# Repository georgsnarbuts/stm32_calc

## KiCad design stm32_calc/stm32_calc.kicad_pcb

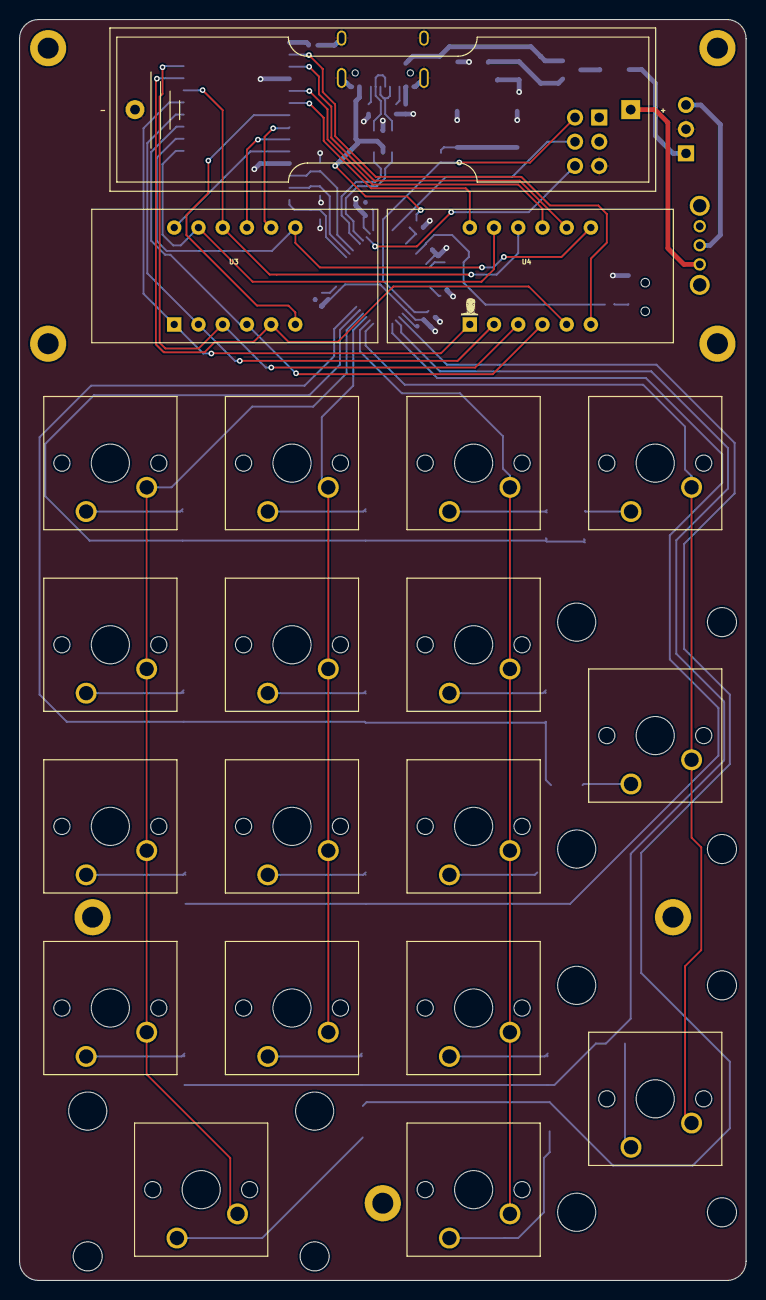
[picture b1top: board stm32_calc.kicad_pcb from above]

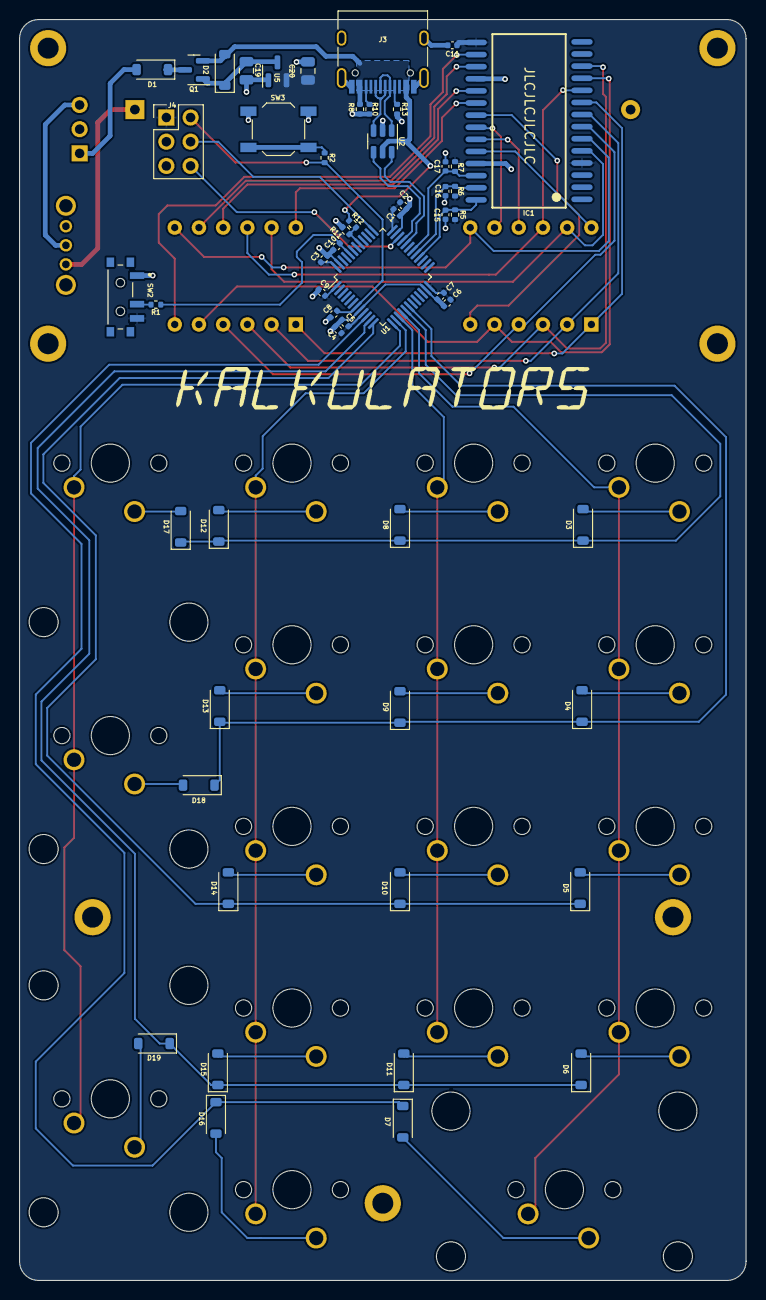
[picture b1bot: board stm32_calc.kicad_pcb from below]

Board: 2 copper layers, 76.2 x 132.2 mm, 83 parts (54 on the bottom side), 66 nets.

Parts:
BT1: Battery_Cell; BatteryHolder_Keystone_2460_1xAA
C1, C3, C6, C9, C11: 100n; C_0402_1005Metric
C2, C7: 4.7u; C_0402_1005Metric
C4: 1u; C_0402_1005Metric
C5: 10n; C_0402_1005Metric
C8, C10: 0.1uF; C_0402_1005Metric
C15, C16, C17: 100pF; C_0402_1005Metric
C19, C20: 1u; C_0805_2012Metric
D1: schottky diode; D_SOD-123
D2: 1n4148; D_SOD-123
D3, D4, D5, D6, D7, D8, D9, D10, D11, D12, D13, D14, D15, D16, D17, D18, D19: 1N4148; D_SOD-123
H1, H2, H3, H4, H5, H6, H7: MountingHole_Pad; MountingHole_2.2mm_M2_DIN965_Pad
IC1: TM1638; SOP28 tm1638
J2: Conn_01x03; PinHeader_1x03_P2.54mm_Vertical
J3: C5307759; USB_C_Receptacle_HRO_TYPE-C-31-M-12
J4: Conn_02x03_Odd_Even; PinHeader_2x03_P2.54mm_Vertical
Q1: p channel mosfet sot 23; SOT-23
R1, R8: 10k; R_0402_1005Metric
R2: 100; R_0402_1005Metric
R5, R6, R7: 10K; R_0402_1005Metric
R10, R13: 5k1; R_0402_1005Metric
R11: 2k; R_0402_1005Metric
R12: 1k; R_0402_1005Metric
SW1: batter_switch; SK12D07VG4_slider
SW2: SS-1290; ss-1290
SW3: Reset; SW_SPST_TL3342
SW_clear1: SW_SPST; geo1.00u_PCB
SW_divide1: SW_SPST; geo1.00u_PCB
SW_eight1: SW_SPST; geo1.00u_PCB
SW_equals1: SW_SPST; geo2.00u_Vertical_PCB
SW_five1: SW_SPST; geo1.00u_PCB
SW_four1: SW_SPST; geo1.00u_PCB
SW_minus1: SW_SPST; geo1.00u_PCB
SW_mutiplicate1: SW_SPST; geo1.00u_PCB
SW_nine1: SW_SPST; geo1.00u_PCB
SW_one1: SW_SPST; geo1.00u_PCB
SW_plus1: SW_SPST; geo2.00u_Vertical_PCB
SW_point1: SW_SPST; geo1.00u_PCB
SW_seven1: SW_SPST; geo1.00u_PCB
SW_six1: SW_SPST; geo1.00u_PCB
SW_three1: SW_SPST; geo1.00u_PCB
SW_two1: SW_SPST; geo1.00u_PCB
SW_zero1: SW_SPST; geo2.00u_PCB
U1: STM32F072CBT6; LQFP-48_7x7mm_P0.5mm
U2: USBLC6-2SC6; SOT-23-6
U3, U4: CC56-12GWA; 7seg_sr410361n
U5: XC6206P332MR; SOT-23

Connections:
+3V3: C1.2, C2.2, C3.2, C4.2, C5.2, C6.2, C7.2, C9.2, C11.1, C20.1, IC1.4 (VCC), IC1.15 (VCC), J4.1, R5.2, R6.2, R7.2, SW2.3 (C), U1.1 (VBAT), U1.9 (VDDA), U1.24 (VDD), U1.36 (VDDIO2), U1.48 (VDD), U5.2 (VO)
+5V: C19.1, D2.1 (K), Q1.1 (D), U5.3 (VI)
BOOT0: C10.1, R1.2, U1.44 (BOOT0)
CLK: C16.2, IC1.27 (CLK), R6.1, U1.29 (TIM1_CH1/PA8)
D+: U1.33 (USB_DP/PA12), U2.4 (I/O2)
D-: U1.32 (USB_DM/TIM1_CH4/PA11), U2.6 (I/O1)
DIO: C17.2, IC1.26 (DIO), R7.1, U1.30 (TIM1_CH2/PA9)
GND: BT1.2 (-), C1.1, C2.1, C3.1, C4.1, C5.1, C6.1, C7.1, C8.2, C9.1, C10.2, C11.2, C15.1, C16.1, C17.1, C19.2, C20.2, IC1.18 (GND), IC1.25 (GND), J2.2, J3.A1 (GND), J3.A12 (GND), J3.B1 (GND), J3.B12 (GND), J3.S1 (SHIELD), J4.5, R8.2, R10.2, R11.1, R13.2, SW2.1 (A), SW3.1, U1.8 (VSSA), U1.23 (VSS), U1.35 (VSS), U1.47 (VSS), U2.2 (GND), U5.1 (GND)
GR1: IC1.5 (SEG1/KS1), U3.11 (a), U4.11 (a)
GR2: IC1.6 (SEG2/KS2), U3.7 (b), U4.7 (b)
GR3: IC1.7 (SEG3/KS3), U3.4 (c), U4.4 (c)
GR4: IC1.8 (SEG4/KS4), U3.2 (d), U4.2 (d)
GR5: IC1.9 (SEG5/KS5), U3.1 (e), U4.1 (e)
GR6: IC1.10 (SEG6/KS6), U3.10 (f), U4.10 (f)
GR7: IC1.11 (SEG7/KS7), U3.5 (g), U4.5 (g)
GR8: IC1.12 (SEG8/KS8), U3.3 (DPX), U4.3 (DPX)
NRST: C8.1, J4.2, R2.2, U1.7 (NRST)
unnamed: BT1.1 (+), SW1.1 (A)
unnamed: D1.2 (A), J2.1
unnamed: D1.1 (K), Q1.3 (S)
unnamed: D3.2 (A), SW_clear1.1 (A)
unnamed: D4.2 (A), SW_seven1.1 (A)
unnamed: D5.2 (A), SW_four1.1 (A)
unnamed: D6.2 (A), SW_one1.1 (A)
unnamed: D7.2 (A), SW_zero1.1 (A)
unnamed: D8.2 (A), SW_divide1.1 (A)
unnamed: D9.2 (A), SW_eight1.1 (A)
unnamed: D10.2 (A), SW_five1.1 (A)
unnamed: D11.2 (A), SW_two1.1 (A)
unnamed: D12.2 (A), SW_mutiplicate1.1 (A)
unnamed: D13.2 (A), SW_nine1.1 (A)
unnamed: D14.2 (A), SW_six1.1 (A)
unnamed: D15.2 (A), SW_three1.1 (A)
unnamed: D16.2 (A), SW_point1.1 (A)
unnamed: D17.2 (A), SW_minus1.1 (A)
unnamed: D18.2 (A), SW_plus1.1 (A)
unnamed: D19.2 (A), SW_equals1.1 (A)
unnamed: J2.3, SW1.2 (B)
unnamed: J3.A5 (CC1), R13.1
unnamed: J3.B5 (CC2), R10.1
unnamed: R2.1, SW3.2
unnamed: R1.1, SW2.2 (B)
SEG1: IC1.24 (GRID1), U3.12 (CC1)
SEG2: IC1.23 (GRID2), U3.9 (CC2)
SEG3: IC1.22 (GRID3), U3.8 (CC3)
SEG4: IC1.21 (GRID4), U3.6 (CC4)
SEG5: IC1.20 (GRID5), U4.12 (CC1)
SEG6: IC1.19 (GRID6), U4.9 (CC2)
SEG7: IC1.17 (GRID7), U4.8 (CC3)
SEG8: IC1.16 (GRID8), U4.6 (CC4)
STB: C15.2, IC1.28 (~STB), R5.1, U1.28 (SPI2_MOSI/I2S2_SD/PB15)
SWCLK: J4.4, U1.37 (SWCLK/PA14)
SWDIO: J4.6, U1.34 (SWDIO/PA13)
col0: SW_clear1.2 (B), SW_four1.2 (B), SW_one1.2 (B), SW_seven1.2 (B), SW_zero1.2 (B), U1.16 (PA6/ADC_IN6/TIM3_CH1/TIM16_CH1)
col1: SW_divide1.2 (B), SW_eight1.2 (B), SW_five1.2 (B), SW_two1.2 (B), U1.15 (PA5/ADC_IN5/DAC_OUT2)
col2: SW_mutiplicate1.2 (B), SW_nine1.2 (B), SW_point1.2 (B), SW_six1.2 (B), SW_three1.2 (B), U1.14 (PA4/TIM14_CH1/ADC_IN4)
col3: SW_equals1.2 (B), SW_minus1.2 (B), SW_plus1.2 (B), U1.13 (PA3/TIM15_CH2/ADC_IN3)
row0: D3.1 (K), D8.1 (K), D12.1 (K), D17.1 (K), U1.17 (PA7/TIM3_CH2/TIM14_CH1/ADC_IN7)
row1: D4.1 (K), D9.1 (K), D13.1 (K), D18.1 (K), U1.18 (PB0/TIM3_CH3/ADC_IN8)
row2: D5.1 (K), D10.1 (K), D14.1 (K), U1.12 (PA2/ADC_IN2)
row3: D6.1 (K), D11.1 (K), D15.1 (K), D19.1 (K), U1.11 (PA1/ADC_IN1)
row4: D7.1 (K), D16.1 (K), U1.10 (PA0/ADC_IN0)
usbD+: J3.A6 (D+), J3.B6 (D+), U2.3 (I/O2)
usbD-: J3.A7 (D-), J3.B7 (D-), U2.1 (I/O1)
usb_check_mcu: R11.2, R12.1, U1.41 (SPI1_MOSI/I2S1_SD/TIM3_CH2/PB5)
vbus: D2.2 (A), J3.A4 (VBUS), J3.A9 (VBUS), J3.B4 (VBUS), J3.B9 (VBUS), Q1.2 (G), R8.1, R12.2, U2.5 (VBUS)

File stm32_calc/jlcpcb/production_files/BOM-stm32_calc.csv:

Comment,Designator,Footprint,LCSC
1k,R12,R_0402_1005Metric,C11702
p channel mosfet sot 23,Q1,SOT-23,C15127
10n,C5,C_0402_1005Metric,C15195
100n,"C1,C10,C11,C3,C6,C8,C9",C_0402_1005Metric,C1525
100pF,"C15,C16,C17",C_0402_1005Metric,C1546
C5307759,J3,USB_C_Receptacle_HRO_TYPE-C-31-M-12,C165948
TM1638,IC1,SOP28 tm1638,C19187
4.7u,"C2,C7",C_0402_1005Metric,C23733
100,R2,R_0402_1005Metric,C25076
10k,"R1,R5,R6,R7,R8",R_0402_1005Metric,C25744
5k1,"R10,R13",R_0402_1005Metric,C25905
USBLC6-2SC6,U2,SOT-23-6,C2687116
1u,"C19,C20",C_0805_2012Metric,C28323
Reset,SW3,SW_SPST_TL3342,C318884
2k,R11,R_0402_1005Metric,C4109
1u,C4,C_0402_1005Metric,C52923
XC6206P332MR ,U5,SOT-23,C5446
SS-1290,SW2,ss-1290,C589295
1N4148,"D10,D11,D12,D13,D14,D15,D16,D17,D18,D19,D2,D3,D4,D5,D6,D7,D8,D9",D_SOD-123,C81598
STM32F072CBT6,U1,LQFP-48_7x7mm_P0.5mm,C81720
schottky diode ,D1,D_SOD-123,C8598

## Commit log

2023-12-04 updated pcb
2023-12-04 added switch and bottom plate
2023-12-05 fixed resistor footprints
2023-12-07 added graphics, fixed some tracing
2023-12-07 fixed routing
